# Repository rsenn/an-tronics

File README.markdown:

40106-4069-Synth \n\n 
555-Oscillator \n\n 
5V-to-12V-Converter \n\n 
Amazing-All-Band-Receiver \n\n 
Amplifier-ClassAB \n\n 
Aurel-super-regen-receiver-ASR2 \n\n 
FM-Radio-Circuit \n\n 
FM-Radio-Simple-Receiver \n\n 
FM-Simple-Regen \n\n 
Headphone-Amplifier-ClassAB-13x7 \n\n 
Headphone-Amplifier-ClassAB-alt3 \n\n 
Headphone-Amplifier-ClassAB-alt4 \n\n 
Headphone-Amplifier-ClassAB-alt \n\n 
Headphone-Amplifier-ClassAB \n\n 
MotorControllerOpto-BA6229 \n\n 
Simple-Analog-Amp-BC547 \n\n 
Simple-Charger-LiIon-OpampBased-LM324-prev \n\n 
Super-Regenerative-FM.old \n\n 
Super-Regenerative-VHF-2Transistor-RickAndersen-October2006-alt \n\n 
Super-Regenerative-VHF-KosmosX3000 \n\n 
Triangulator-LM324 \n\n 
VCF-LM324-Stereo+LFO-CableConn \n\n 
Simple-NPN-Regen-Receiver \n\n

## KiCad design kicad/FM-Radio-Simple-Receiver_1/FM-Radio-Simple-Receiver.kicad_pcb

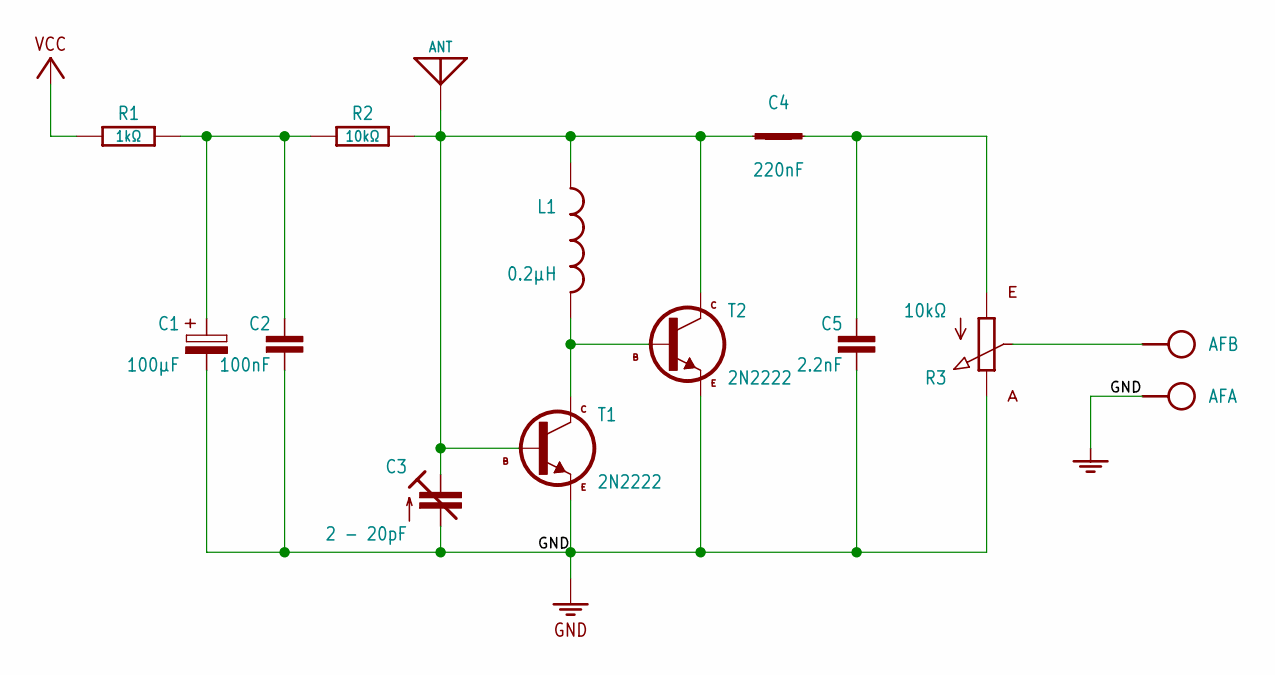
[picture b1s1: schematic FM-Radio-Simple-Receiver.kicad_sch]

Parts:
AF: SPAD+-+-; SPAD+-
ANT: ANT; SPAD
BAT: VCC_GNDL; SPAD-+
C1: 100µF; E2,5-5_V
C2: 100nF; C050-020X036_V
C3: 2 - 20pF; TRIM-2222-808
C4: 220nF; C050-020X044
C5: 2.2nF; C050-020X036_V
L1: 0.2µH; L-10_10X
R1: 1kΩ; 0204_10
R2: 10kΩ; 0204_10
R3: 10kΩ; POT
T1, T2: 2N2222; TO92

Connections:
GND: AF.1, BAT.1 (GND), C1.-, C2.2, C3.2 (A), C5.2, R3.E, T1.1 (E), T2.1 (E)
unnamed: ANT.1, C3.3 (E), C4.1, L1.P$1 (1), R2.2, T1.2 (B), T2.3 (C)
unnamed: C1.+, C2.1, R1.2, R2.1
unnamed: C4.2, C5.1, R3.A
unnamed: L1.P$2 (2), T1.3 (C), T2.2 (B)
unnamed: AF.2, R3.S
VCC: BAT.2 (VCC), R1.1

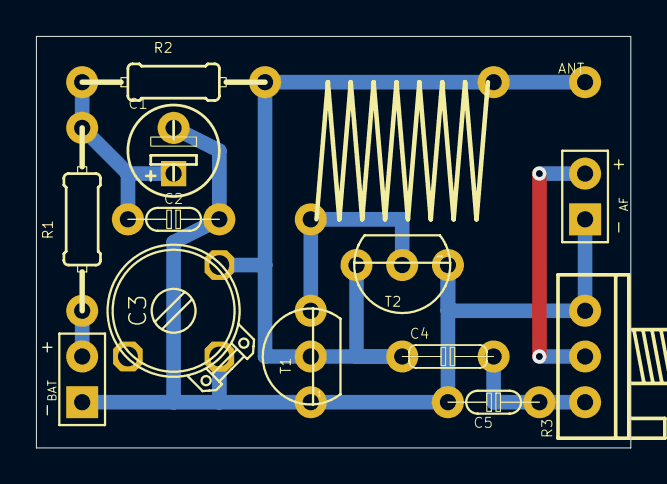
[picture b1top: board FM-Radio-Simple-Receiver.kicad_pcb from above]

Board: 2 copper layers, 33.0 x 22.9 mm, 14 parts (0 on the bottom side), 7 nets.

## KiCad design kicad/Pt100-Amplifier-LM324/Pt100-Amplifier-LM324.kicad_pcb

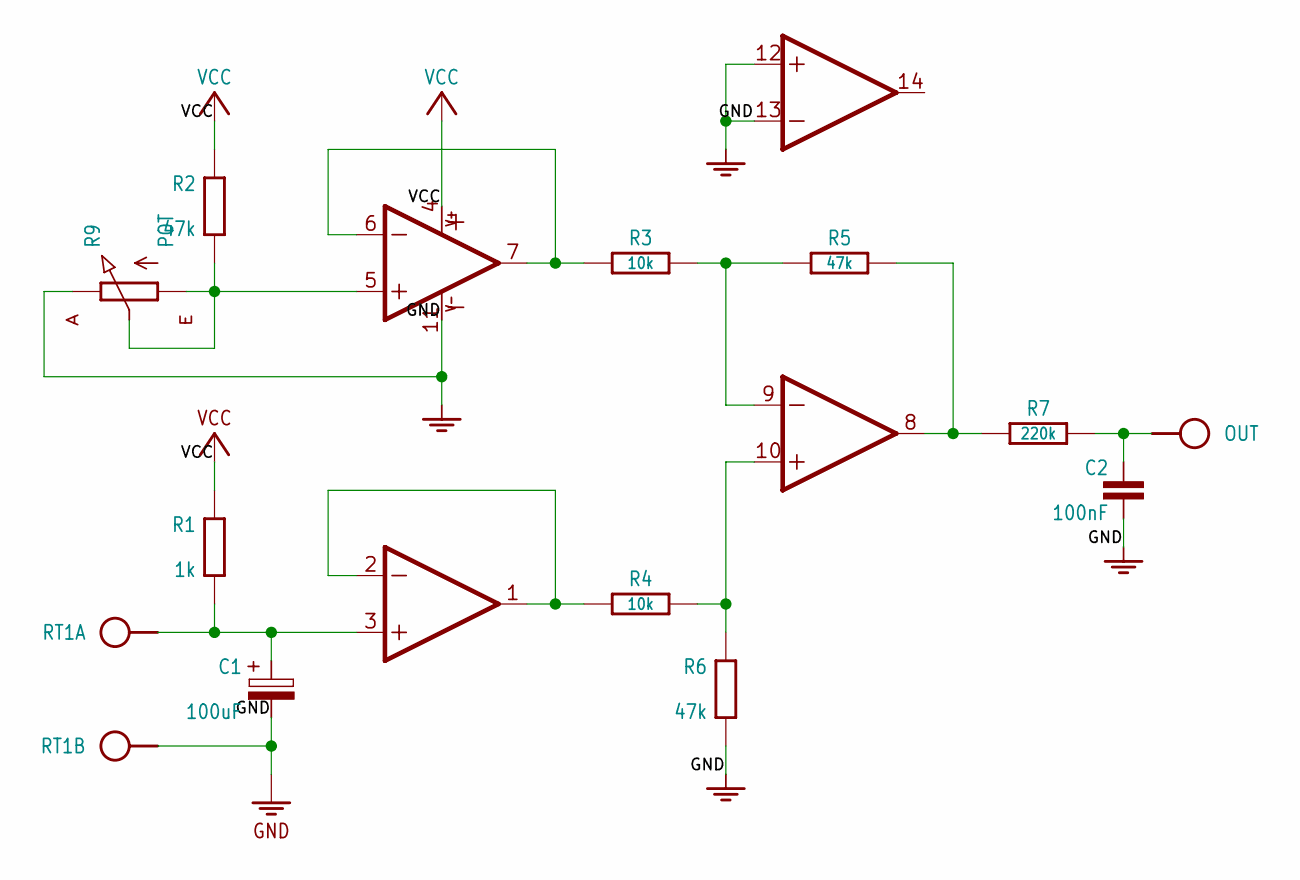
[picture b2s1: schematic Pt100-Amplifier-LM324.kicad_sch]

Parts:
C1: 100uF; E2,5-5
C2: 100nF; C050-020X044_V
IC1: LM324-LM324; DIL14-LM324
OUT: HPORT; SPAD
R1: 1k; 0204_10
R2: 47k; 0204_10
R3: 10k; 0204_10-V
R4: 10k; 0204_15
R5, R6: 47k; 0204_10-V
R7: 220k; 0204_10
R9: POT
RT1: SPAD-2
S5: VCC_GNDPWR-L; PWR-L

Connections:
GND: C1.-, C2.2, IC1.11 (V-), IC1.12 (+IN), IC1.13 (-IN), R6.2 (1), R9.E, RT1.2, S5.1 (GND)
unnamed: C1.+, IC1.3 (+IN), R1.2 (1), RT1.1
unnamed: IC1.1 (OUT), IC1.2 (-IN), R4.1
unnamed: IC1.10 (+IN), R4.2, R6.1 (2)
unnamed: IC1.9 (-IN), R3.2, R5.1
unnamed: IC1.8 (OUT), R5.2, R7.1
unnamed: C2.1, OUT.1, R7.2
unnamed: IC1.6 (-IN), IC1.7 (OUT), R3.1
unnamed: IC1.5 (+IN), R2.2 (1), R9.A, R9.S
VCC: IC1.4 (V+), R1.1 (2), R2.1 (2), S5.2 (VCC)

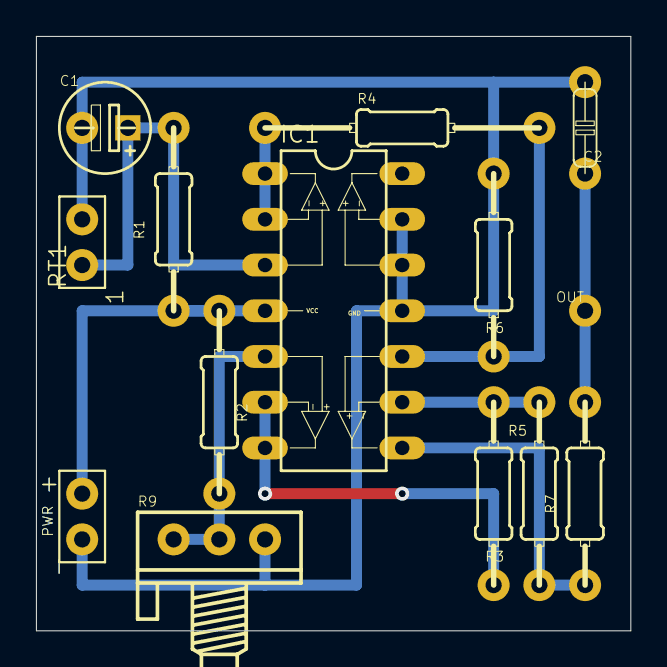
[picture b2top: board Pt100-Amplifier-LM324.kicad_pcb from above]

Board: 2 copper layers, 33.0 x 33.0 mm, 14 parts (0 on the bottom side), 10 nets.

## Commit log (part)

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2020-04-30 updated libraries
2021-05-27 removed polygons
